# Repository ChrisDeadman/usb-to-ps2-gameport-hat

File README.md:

Usb => PS/2 & Gameport HAT v1.4
===============================

Author: ChrisDeadman

Convert USB devices to PS/2 & Gameport devices with the power of Arduino 🙂

## Supported input devices
* HID Mouse
* HID Keyboard
* HID Mouse / Keyboard Combo
* HID Joystick / Gamepad\*
* Xbox 360 Controller\*\*

\* *Descriptor parsing is a work in progress and may not work for all devices.*  
\*\* *Currently, only the Xbox 360 Wireless Receiver is supported.*

## Outputs
* PS/2 Mouse\* port
* PS/2 Keyboard\*\* / Mouse combined port
* Gameport

\* *All types are supported, including IntelliMouse (5 Buttons + Scroll wheel).*  
\*\* *Scancode Set 2*

## Supported Arduino Boards
* [SparkFun SAMD21 Mini Breakout](https://www.sparkfun.com/products/13664)\*

\* *Other ATSAMD21G18 boards should also work well, provided they have the same pinout.*

## Usage

* Power the board using a USB cable and set the **Power select** jumper to **USB**.  
  **Alternative:** Set **Power select** jumper to **Gameport**. Be aware that the current is limited depending on the host machine.

* Use a USB OTG cable to connect your USB device to the Arduino.  
  **Recommendation:** Connect a USB hub to the Arduino if you want to use multiple USB devices.

## LEDs

* **LED1** is **ON** if the host inhibits any PS/2 port.
* **LED1** is **FLASHING** if data transfer occurs over any PS/2 port.
* **LED2** indicates **Joy Button** press or the highest **Axis Value**.

## Input Mappings

### USB -> Gameport

This is how USB Joysticks / Gamepads are mapped to the Gameport:

| Joystick 1            | Joystick 2        | Gameport |
|:----------------------|:------------------|:---------|
| X-Axis 1 / D-Pad      | -                 | X-Axis 1 |
| Y-Axis 1 / D-Pad      | -                 | Y-Axis 1 |
| X-Axis 2              | X-Axis 1 / D-Pad  | X-Axis 2 |
| Y-Axis 2              | Y-Axis 2 / D-Pad  | Y-Axis 2 |
| Button 1 / A / R2     | -                 | Button 1 |
| Button 2 / B / L2     | -                 | Button 2 |
| Button 3 / X / Select | Button 1 / A / R2 | Button 3 |
| Button 4 / Y / Start  | Button 2 / B / L2 | Button 4 |

### Emulation Mode Mappings

Consult the table below to understand the mapping between various device inputs when an emulation mode is enabled:

| Keyboard            | Mouse        | Joystick                      | Gameport |
|:--------------------|:-------------|:------------------------------|:---------|
| Left / Right Arrow  | X-Axis       | X-Axis 1 / D-Pad              | X-Axis 1 |
| Up / Down Arrow     | Y-Axis       | Y-Axis 1 / D-Pad              | Y-Axis 1 |
| A / D               | -            | X-Axis 2                      | X-Axis 2 |
| W / S               | Scroll wheel | Y-Axis 2                      | Y-Axis 2 |
| L-Ctrl / R-Ctrl     | Button 1     | Button 1 / A                  | Button 1 |
| Space / R-Shift     | Button 2     | Button 2 / B                  | Button 2 |
| L-Alt / CapsLock    | Button 3     | Button 3 / X                  | Button 3 |
| L-Shift             | Button 4     | Button 4 / Y                  | Button 4 |
| Period              | Button 5     | Button 5 / R1                 | -        |
| Comma               | -            | Button 6 / L1                 | -        |
| Up Arrow            | -            | Button 7 / R2                 | -        |
| Down Arrow          | -            | Button 8 / L2                 | -        |
| Escape              | -            | Button 9 / SELECT             | -        |
| Tab                 | -            | Button 10 / START             | -        |

#### Here are a few examples:

* **Joystick -> Keyboard** Emulation Mode:  
  Moving the joystick along X-Axis 1 *(or D-Pad left and right)* acts as if you pressed the Left / Right Arrow keys on the keyboard.

* **Joystick -> Mouse** Emulation Mode:  
  Moving the joystick along X-Axis 1 *(or D-Pad left and right)* move the mouse cursor along the X-Axis.

* **Keyboard -> Joystick** Emulation Mode:  
  If **L-CTRL** or **R-CTRL** is pressed, it acts as if you pressed Button 1 on the joystick.

* **Keyboard -> Mouse** Emulation Mode:  
  The Left / Right Arrow keys on your keyboard move the mouse cursor along the X-Axis.

* **Mouse -> Joystick** Emulation Mode:  
  Moving the mouse left and right corresponds to moving the joystick along the X-Axis 1.

## Setup Mode

Enter this mode to enable special features. Note that those settings are reset to default when the device is reset.

#### Feedback

* **LED1** blink count indicates the current setting.
* **LED2** blink count indicates the value of the current setting, blinks only in edit mode.
* Keyboard LEDs will also blink accordingly (**LED1**=**CapsLock**, **LED2**=**NumLock** and **ScrollLock**).
* LEDs of supported controllers (e.g. Xbox 360) will also blink accordingly.

#### Settings

| Setting               | LED1 Blinks | Values / LED2 Blinks                 | Default |
|:----------------------|:-----------:|:-------------------------------------|:-------:|
| Emulation Mode        | 1           | **OFF**                              | **OFF** |
|                       |             | **1**  Joystick -> Keyboard          |         |
|                       |             | **2**  Joystick -> Mouse             |         |
|                       |             | **3**  Keyboard -> Joystick          |         |
|                       |             | **4**  Keyboard -> Mouse             |         |
|                       |             | **5**  Mouse    -> Joystick          |         |
| Swap joy axis 3 and 4 | 2           | **ON** / **OFF**                     | **OFF** |
| Mouse Emu Speed       | 3           | **1 <= n <= 255**                    | **2**   |

#### Key bindings

| Keyboard        | Joystick / Gamepad            | Function                                          |
|:----------------|:------------------------------|:--------------------------------------------------|
| CTRL+SHIFT+WIN  | Button 5 / R1 + Button 6 / L1 | Hold for ~1s to enter/exit setup mode             |
| Return          | Button 1 / A                  | Edit setting / exit edit mode                     |
| Right Arrow     | X-Axis 1 / D-PAD Right        | Next setting / increase value (edit mode)         |
| Left Arrow      | X-Axis 1 / D-PAD Left         | Prev. setting / decrease value (edit mode)        |
| ESC             | Button 9 / SELECT             | Apply Default Settings and exit setup mode        |
| F1              | -                             | Set Emulation Mode #1 and exit setup mode         |
| F2              | -                             | Set Emulation Mode #2 and exit setup mode         |
| F3              | -                             | Set Emulation Mode #3 and exit setup mode         |
| F4              | -                             | Set Emulation Mode #4 and exit setup mode         |
| F5              | -                             | Set Emulation Mode #5 and exit setup mode         |
| F6              | -                             | Toggle Swap joy axis 3 and 4 and exit setup mode  |
| F7              | -                             | Decrease Mouse Emu Speed and exit setup mode      |
| F8              | -                             | Increase Mouse Emu Speed and exit setup mode      |

## Flashing the firmware

* Install drivers for you serial adapter
* Connect the **SAMD21 Mini Breakout** to your computer  
*(either via USB OTG cable or via the Debug Conn. pins using a USB<->Serial converter)*
* Double-Tap the reset button on the board to enter bootloader mode

### Automatically

* [Download and run latest firmware_flash.bat](https://github.com/ChrisDeadman/usb-to-ps2-gameport-hat/releases/latest)

### Manually

* [Download latest firmware.bin](https://github.com/ChrisDeadman/usb-to-ps2-gameport-hat/releases/latest)
* [Download Bossa](https://www.shumatech.com/web/products/bossa)
* Flash with `bossac --port=/dev/ttyUSB0 -U -i --offset=0x2000 -e -w firmware.bin -R`

*Ensure you change `--port` to match your system's actual port. The example provided is for Linux systems.*

## Developer Notes

* Diagnostic information is available via **Debug Conn. @ 115200 8N1**  
  *Sending any character returns sent/received data and device status.*

* Enable USB Debugging in `USB.h` *(in USB_Host_Library_SAMD)* by uncommenting `#define DEBUG_USB_HOST 1` and setting `#define USB_HOST_SERIAL` to `SERIAL_PORT_HARDWARE`.

* You can change pins in `include/Config.h`.

* You can add support for additional USB devices by implementing a `JoystickDriverMapper` and adding it to `joy_mappers` in `main.cpp`.

Schematic
=========

Layout
======

Upside
======

Backside
========

Release notes
=============

### Usb => PS/2 & Gameport HAT v1.4
* Add keyboard support
* Add device emulation modes
* @Ulfenknulfen: Fix Joy Axes hardware bug which limited axes range and fixes calibration issues
* Rework and document setup mode
* Rework device input combining
* Always signal inhibited state with LED1
* Improve serial logging

### Usb => PS/2 & Gameport HAT v1.3
* @Ulfenknulfen: Make secondary PS/2 connector a combined connector
* @Ulfenknulfen: PCB layout improvements

### Usb => PS/2 & Gameport HAT v1.2
* Add a second PS/2 port to support keyboards in the future

### Usb => PS/2 & Gameport HAT v1.1
* Fix incorrect PS/2 pin connections

### Usb => PS/2 & Gameport HAT v1.0
* Initial version

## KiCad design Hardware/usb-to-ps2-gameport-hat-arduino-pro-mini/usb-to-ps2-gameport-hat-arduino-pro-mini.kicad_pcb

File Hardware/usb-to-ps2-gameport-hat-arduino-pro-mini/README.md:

Usb => PS/2 & Gameport HAT v1.4
===============================

## Where to order which parts?
You can generate a BOM (bill of materials) from within KiCad in order to easily see the parts you need.

I made sure to pick parts with good availability so I could order all of them at once at [Mouser](https://mouser.com).

## Where to order the PCB?
Pretty much all manufacturers should support KiCad or Gerber formats.

I ordered at [EuroCircuits](https://be.eurocircuits.com/) for this project but e.g. [JLCPCB](https://jlcpcb.com/) should also be fine!

## How to generate gerber files?
Pre-generated gerber files are [here](https://github.com/ChrisDeadman/usb-to-ps2-gameport-hat/tree/master/Hardware/usb-to-ps2-gameport-hat-arduino-pro-mini/Gerberfiles_RTU/Gerber_RTU.zip).

Should you want to generate them yourself, you need to install [KiCad](https://kicad-pcb.org/) to open the project and export the gerber files,
[JLCPCB](https://support.jlcpcb.com/article/44-how-to-export-kicad-pcb-to-gerber-files) has a nice tutorial of how to do that.

## How to solder?
If you order a stencil with your PCB you can use a normal oven to solder the stuff in place - in this case I would still solder the "big" elco manually afterwards because of heat concerns.

I did solder everything manually tho using the soldering iron I use for normal prototyping, just make sure to use a lot of flux for the ICs to avoid shorting the pins - and best triple-check afterwards that you didn't 😉

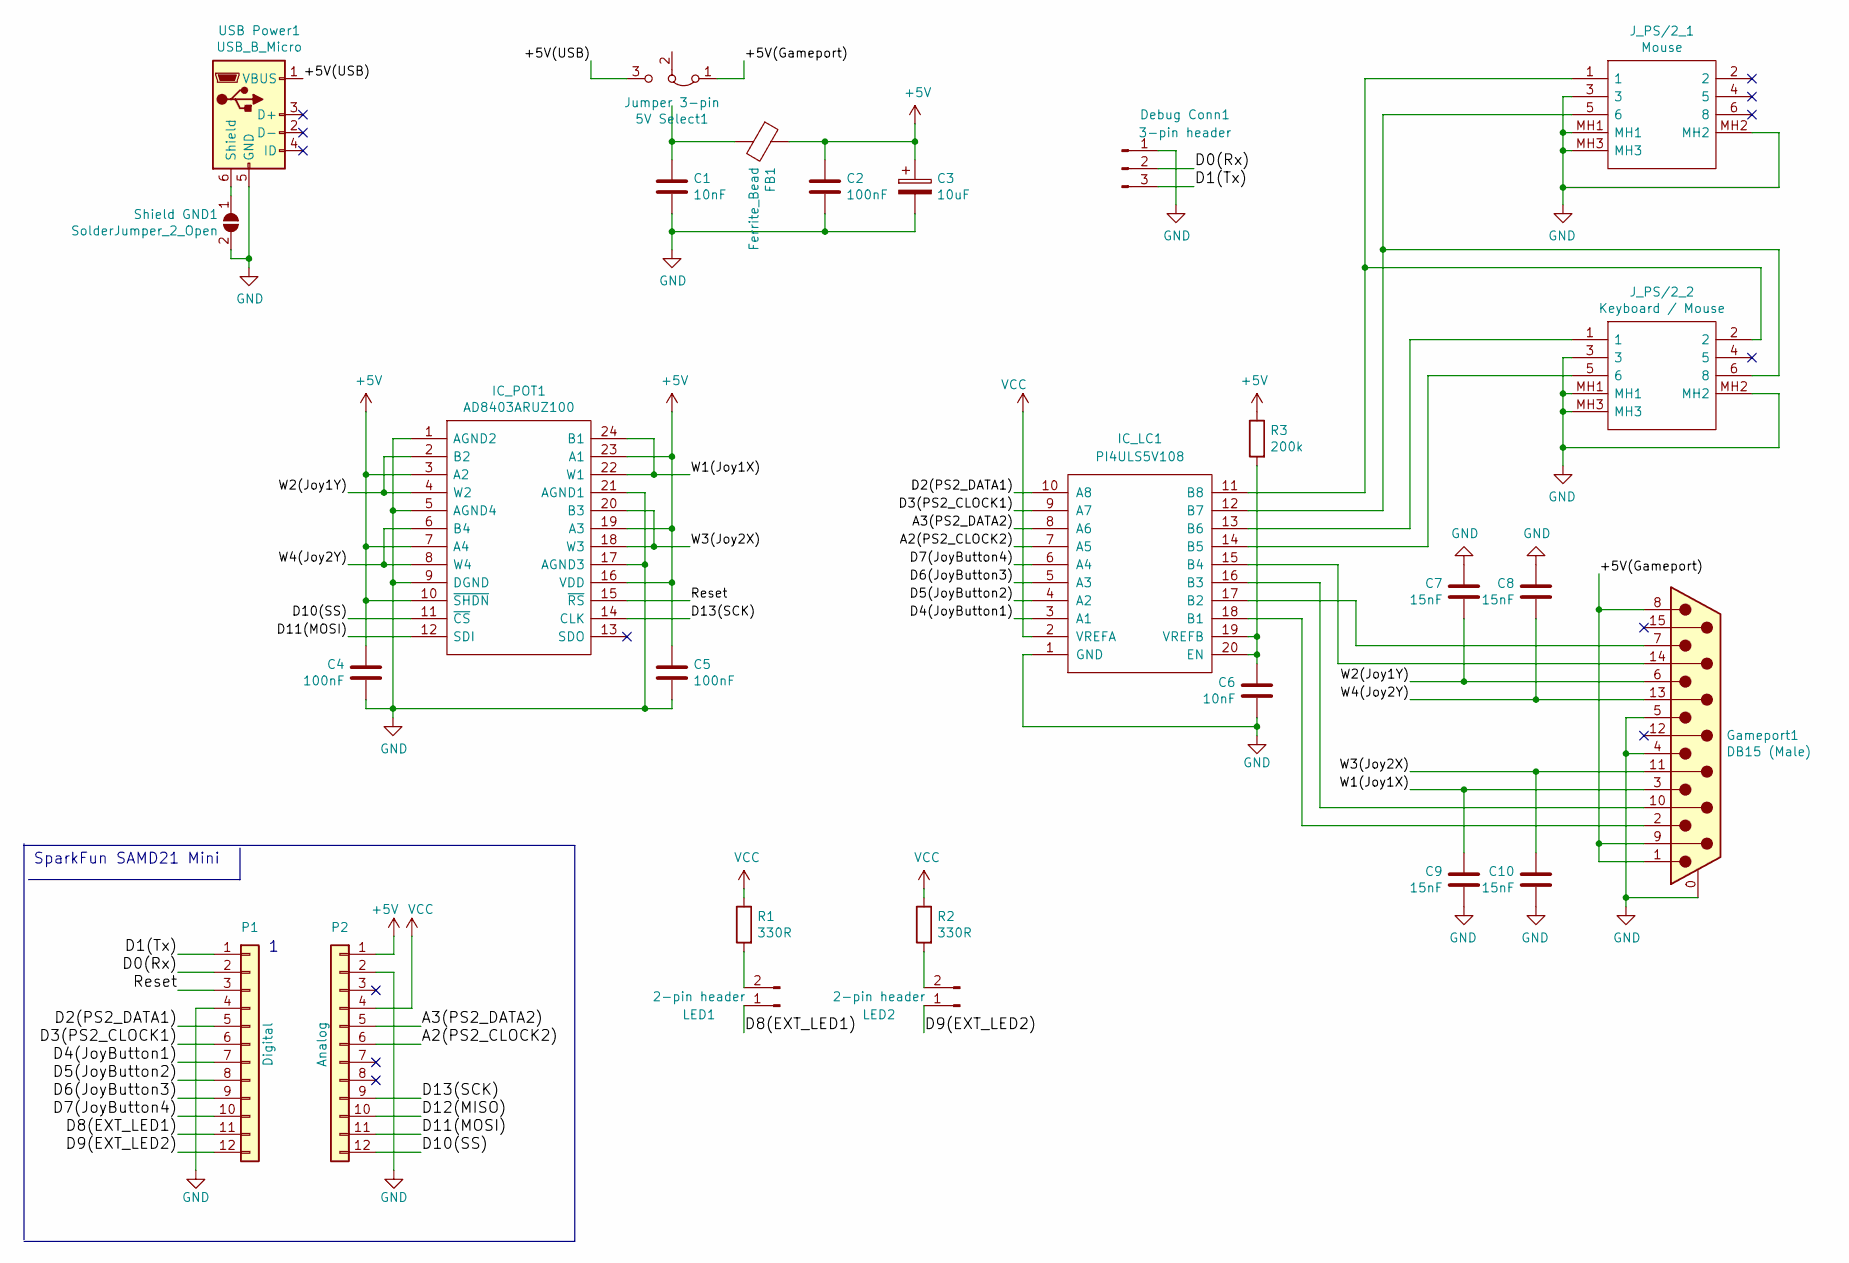
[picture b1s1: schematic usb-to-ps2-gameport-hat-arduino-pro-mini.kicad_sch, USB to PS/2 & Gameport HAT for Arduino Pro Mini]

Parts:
5V Select1: Jumper 3-pin; PinHeader_1x03_P2.54mm_Vertical
C1, C6: 10nF; C_0603_1608Metric
C2, C4, C5: 100nF; C_0603_1608Metric
C3: 10uF; CP_Elec_4x5.4
C7, C8, C9, C10: 15nF; C_0603_1608Metric
Debug Conn1: 3-pin header; PinHeader_1x03_P2.54mm_Vertical
FB1: Ferrite_Bead; L_0603_1608Metric
Gameport1: DB15 (Male); DSUB-15_Male_Horizontal_P2.77x2.84mm_EdgePinOffset7.70mm_Ho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
IC_LC1: PI4ULS5V108; TSSOP-20_4.4x6.5mm_P0.65mm
IC_POT1: AD8403ARUZ100; SOP65P640X120-24N; Mouser Part Number 584-AD8403ARUZ100
J_PS/2_1: Mouse; KMDGX6SBS; Mouser Part Number 806-KMDGX-6S-BS
J_PS/2_2: Keyboard / Mouse; KMDGX6SBS; Mouser Part Number 806-KMDGX-6S-BS
LED1, LED2: 2-pin header; PinHeader_1x02_P2.54mm_Vertical
P1: Digital; PinSocket_1x12_P2.54mm_Vertical
P2: Analog; PinSocket_1x12_P2.54mm_Vertical
R1, R2: 330R; R_0603_1608Metric
R3: 200k; R_0603_1608Metric
Shield GND1: SolderJumper_2_Open; SolderJumper-2_P1.3mm_Open_RoundedPad1.0x1.5mm
USB Power1: USB_B_Micro; USB_Micro-B_Molex-105017-0001

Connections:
+5V: C2.1, C3.1, C4.1, C5.1, FB1.1, IC_POT1.3 (A2), IC_POT1.7 (A4), IC_POT1.10 (~SHDN), IC_POT1.16 (VDD), IC_POT1.19 (A3), IC_POT1.23 (A1), P2.1, R3.1
/+5V(Gameport): 5V Select1.1 (A), Gameport1.1, Gameport1.8, Gameport1.9
/+5V(USB): 5V Select1.3 (B), USB Power1.1 (VBUS)
/A2(PS2_CLOCK2): IC_LC1.7 (A5), P2.6
/A3(PS2_DATA2): IC_LC1.8 (A6), P2.5
/D0(Rx): Debug Conn1.2, P1.2
/D1(Tx): Debug Conn1.3, P1.1
/D2(PS2_DATA1): IC_LC1.10 (A8), P1.5
/D3(PS2_CLOCK1): IC_LC1.9 (A7), P1.6
/D4(JoyButton1): IC_LC1.3 (A1), P1.7
/D5(JoyButton2): IC_LC1.4 (A2), P1.8
/D6(JoyButton3): IC_LC1.5 (A3), P1.9
/D7(JoyButton4): IC_LC1.6 (A4), P1.10
/D8(EXT_LED1): LED1.1, P1.11
/D9(EXT_LED2): LED2.1, P1.12
/D10(SS): IC_POT1.11 (~CS), P2.12
/D11(MOSI): IC_POT1.12 (SDI), P2.11
/D12(MISO): P2.10
/D13(SCK): IC_POT1.14 (CLK), P2.9
/Reset: IC_POT1.15 (~RS), P1.3
/W1(Joy1X): C9.1, Gameport1.3, IC_POT1.22 (W1), IC_POT1.24 (B1)
/W2(Joy1Y): C7.2, Gameport1.6, IC_POT1.2 (B2), IC_POT1.4 (W2)
/W3(Joy2X): C10.1, Gameport1.11 (P111), IC_POT1.18 (W3), IC_POT1.20 (B3)
/W4(Joy2Y): C8.2, Gameport1.13, IC_POT1.6 (B4), IC_POT1.8 (W4)
GND: C1.2, C2.2, C3.2, C4.2, C5.2, C6.2, C7.1, C8.1, C9.2, C10.2, Debug Conn1.1, Gameport1.0 (PAD), Gameport1.4, Gameport1.5, IC_LC1.1 (GND), IC_POT1.1 (AGND2), IC_POT1.5 (AGND4), IC_POT1.9 (DGND), IC_POT1.17 (AGND3), IC_POT1.21 (AGND1), J_PS/2_1.3, J_PS/2_1.MH1, J_PS/2_1.MH2, J_PS/2_1.MH3, J_PS/2_2.3, J_PS/2_2.MH1, J_PS/2_2.MH2, J_PS/2_2.MH3, P1.4, P2.2, Shield GND1.2 (B), USB Power1.5 (GND)
unnamed: Gameport1.10, IC_LC1.16 (B3)
unnamed: Gameport1.14, IC_LC1.15 (B4)
unnamed: Gameport1.2, IC_LC1.18 (B1)
unnamed: Gameport1.7, IC_LC1.17 (B2)
unnamed: IC_LC1.14 (B5), J_PS/2_2.5 (6)
unnamed: IC_LC1.13 (B6), J_PS/2_2.1
unnamed: IC_LC1.12 (B7), J_PS/2_1.5 (6), J_PS/2_2.6 (8)
unnamed: IC_LC1.11 (B8), J_PS/2_1.1, J_PS/2_2.2
unnamed: C6.1, IC_LC1.19 (VREFB), IC_LC1.20 (EN), R3.2
unnamed: LED1.2, R1.2
unnamed: LED2.2, R2.2
unnamed: Shield GND1.1 (A), USB Power1.6 (Shield)
VCC: IC_LC1.2 (VREFA), P2.4, R1.1, R2.1

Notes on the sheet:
SparkFun SAMD21 Mini

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
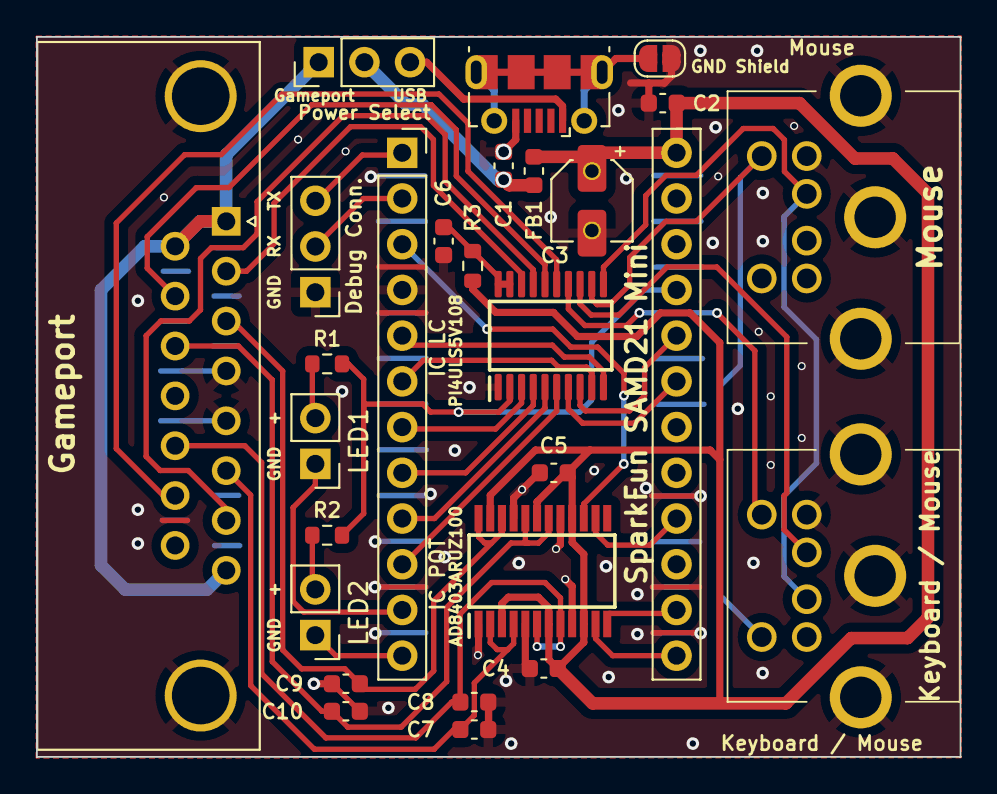
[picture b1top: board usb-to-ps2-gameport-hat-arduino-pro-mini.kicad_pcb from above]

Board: 2 copper layers, 51.3 x 40.0 mm, 27 parts (0 on the bottom side), 38 nets.

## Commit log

2019-10-20 Correct the version in readme and add history
2020-01-15 Add hardware related Readme containing FAQ
2020-02-22 fix issue with mouse scrollwheel in 5-button mode
2022-02-04 add schematic image
2022-02-04 update to KiCad 6
2024-01-12 redesign setup mode, remove deadzone
2024-01-12 add support for multiple PS/2 ports
2024-01-12 fix issues with CircularBuffer
2024-01-12 Add keyboard support :)
2024-01-13 add keyboard bindings for setup mode
2024-01-13 improve logging format
2024-01-13 keep PS/2 clock IRQ enabled
2024-01-13 exclude keys w/o brk code from typematic handling
2024-01-13 speed up GlobalStringBuffer
2024-01-13 get rid of manual inline
2024-01-13 also log USB packets in debug mode
2024-01-20 support kbleds in setupmode + blink instead of dim
2024-01-20 don't set led status on not connected devices
2024-01-20 PS/2 is not busy if inhibited
2024-01-20 fix inverted led state in logging
2024-01-20 always signal inhibited state with LED1
2024-01-20 fix buffer overflow bug in GlobalStringBuffer
2024-01-21 combine all secondary joy inputs
2024-01-21 Initialize keyboard driver before HID universal
2024-01-21 Use updated drivers for is_connected check
2024-01-22 README improvements
2024-01-24 implement virtual devices
2024-01-24 support 8 virtual joy buttons
2024-01-26 streamline controller states
2024-01-26 implement device emulation modes
2024-01-26 enable secondary KB emu keys
2024-01-26 add missing PS/2 keyboard ACKs
2024-01-26 speed up device initialization
2024-01-26 simplify KB_EMU_MAPPINGS
2024-01-26 joy emulation should work for 2 players
2024-01-26 simplify and move AXIS_TO_POT_VALUE to config
2024-01-27 Use both ScrollLock and NumLock as LED2
2024-01-29 ensure correct order of MAKE/BREAK codes
2024-02-05 Fix some joystick axis scaling issues
2024-02-05 fix various issues with emulation modes
2024-02-10 support Xbox 360 controller LEDs during setup mode
2024-02-11 fix PS/2 mouse detection issues
2024-02-11 fix PS/2 mouse movement package
2024-02-13 Fix PS/2 resend behavior after inhibit
2024-02-14 fix some PS/2 timing issues
2024-02-14 remove logging calls from ISR
2024-02-14 mouse should only report most recent movement
2024-02-17 fix inconsistent clock timing
2024-02-19 implement common key buffer, reduce KRO to 3
2024-02-19 always release data pin
2024-02-19 properly acquire/release PS/2 pins
2024-02-19 fix PS/2 device busy during multi-byte responses
2024-02-19 optimize for speed rather than codesize
2024-02-20 fix PS/2 inhibit behavior
2024-02-21 limit number of led flashes for XBOX Controller
2024-02-21 enable all buttons of secondary controllers
2024-02-29 properly align report buffer for keyboard leds
2024-02-29 new hardware revision: unlock full range of gameport axes
2024-03-01 implement Paddy's wishlist ;)
2024-03-01 limit update rate of all LEDs
2024-03-01 fix setup mode blinking issues
2024-03-08 fix mouse emulation modes + add speed setting
2024-03-08 @Ulfenknulfen: connect base of digi-pot with wiper
2024-03-08 add setup-mode quick-keys for mouse emu speed
2024-03-09 prepare Release V1.4
2024-03-10 Add more information to Readme
2024-03-21 fix PS2Port::disable_clock_irq()
2024-03-21 increase keyboard buffer and support more BREAK codes
2024-03-21 add firmware_flash.bat script
2024-10-20 potential fix for mouse not working under DOS for some chipsets
    don't set overflow bits in mouse packets
    only send PS/2 mouse state if actually changed
2024-10-20 rework keyboard buffer and support more BREAK codes
    increase key-rollover from 3 to 6
2024-11-09 rework hid keyboard parsing and increase key-rollover
2025-03-16 fix overflow bits in mouse packets
    only send PS/2 mouse state if actually changed

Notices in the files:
Hardware/usb-to-ps2-gameport-hat-arduino-pro-mini/usb-to-ps2-gameport-hat-arduino-pro-mini.kicad_pcb:
© 2024 by Deadman
V1.4 © 2024 by Hubsi
